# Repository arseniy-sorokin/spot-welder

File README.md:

# spot-welder
Spot welder controller for Warsaw Hackerspace (hackerspace.pl)

Based on work of Albert van Dalen http://www.avdweb.nl/arduino/hardware-interfacing/spot-welder-controller.html

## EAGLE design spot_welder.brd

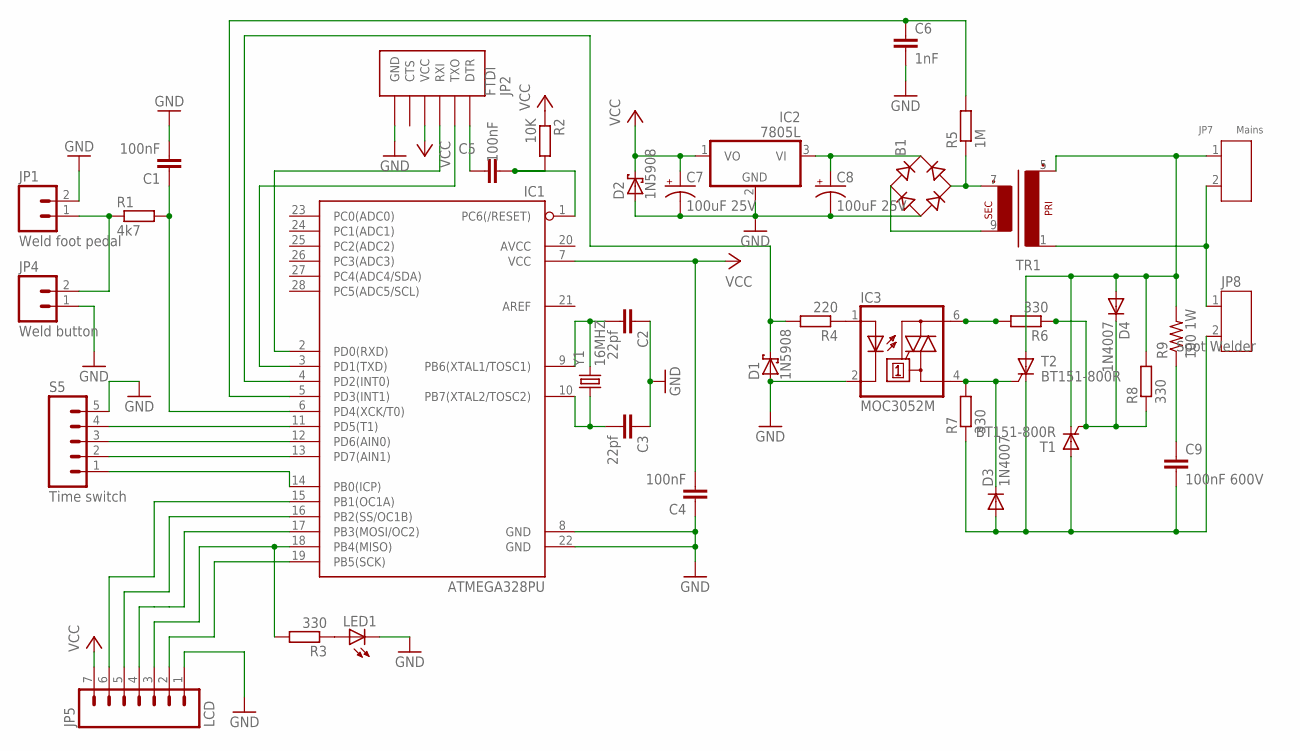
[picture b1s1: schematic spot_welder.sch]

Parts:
B1: B-DIL
C1: 100nF; CAP-PTH-5MM
C2, C3: 22pf; C025-024X044
C4, C5: 100nF; C025-024X044
C6: 1nF; C025-024X044
C7, C8: 100uF 25V; CPOL-RADIAL-100UF-25V
C9: 100nF 600V; C15B5
D1, D2: 1N5908; C4111-15
D3, D4: 1N4007; DO41-10
IC1: ATMEGA328PU; DIL28-3
IC2: 7805L; TO92
IC3: MOC3052M; DIL06
JP1: Weld foot pedal; 1X02_LOCK
JP2: FTDI; FTDI_DEVICE_SIDE
JP4: Weld button; 1X02_LOCK
JP5: LCD; 1X07_NO_SILK
JP7: Mains; H2-5.0-10.5X8.0MM
JP8: Spot Welder; H2-5.0-10.5X8.0MM
LED1: LEDLD260; LD260
R1: 4k7; 0204/7
R2: 10K; 0204/7
R3, R6, R7, R8: 330; 0204/7
R4: 220; 0204/7
R5: 1M; 0204/7
R9: 100 1W; AXIAL-0.6
S5: Time switch; 1X05_NO_SILK
T1, T2: BT151-800R; TO220CS
TR1: EI30-1
Y1: 16MHZ; HC49/S

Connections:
GND: B1.-, C1.2, C2.1, C3.1, C4.1, C6.2, C7.2 (-), C8.2 (-), D1.A, D2.A, IC1.8 (GND), IC1.22 (GND), IC2.2 (GND), IC3.2 (C), JP1.2, JP2.P$6 (GND), JP4.1, JP5.1, LED1.K (C), S5.5
unnamed: B1.AC2, R5.1, TR1.7 (S3)
unnamed: B1.+, C8.1 (+), IC2.3 (VI)
unnamed: C9.2, D3.A, JP8.2, R7.1, T1.A, T2.C
unnamed: B1.AC1, TR1.9 (S4)
unnamed: JP7.2, JP8.1, TR1.1
unnamed: D3.C, IC3.4 (A1), R7.2, T2.G
unnamed: C5.1, JP2.P$1 (DTR)
unnamed: IC3.6 (A2), R6.2
unnamed: IC3.1 (A), R4.1
unnamed: D4.A, JP7.1, R8.2, R9.P$2 (2), T1.C, T2.A, TR1.5 (P2)
unnamed: C9.1, R9.P$1 (1)
unnamed: D4.C, R6.1, R8.1, T1.G
unnamed: C6.1, IC1.5 (PD3(INT1)), R5.2
unnamed: C5.2, IC1.1 (PC6(/RESET)), R2.2
unnamed: D1.C, IC1.4 (PD2(INT0)), R4.2
unnamed: C2.2, IC1.9 (PB6(XTAL1/TOSC1)), Y1.2
unnamed: C3.2, IC1.10 (PB7(XTAL2/TOSC2)), Y1.1
unnamed: IC1.11 (PD5(T1)), S5.4
unnamed: IC1.3 (PD1(TXD)), JP2.P$2 (TXO)
unnamed: IC1.2 (PD0(RXD)), JP2.P$3 (RXI)
unnamed: JP1.1, JP4.2, R1.1
unnamed: C1.1, IC1.6 (PD4(XCK/T0)), R1.2
unnamed: IC1.12 (PD6(AIN0)), S5.3
unnamed: IC1.13 (PD7(AIN1)), S5.2
unnamed: IC1.14 (PB0(ICP)), S5.1
unnamed: LED1.A, R3.1
unnamed: IC1.18 (PB4(MISO)), JP5.3, R3.2
unnamed: IC1.15 (PB1(OC1A)), JP5.6
unnamed: IC1.16 (PB2(SS/OC1B)), JP5.5
unnamed: IC1.17 (PB3(MOSI/OC2)), JP5.4
unnamed: IC1.19 (PB5(SCK)), JP5.2
VCC: C4.2, C7.1 (+), D2.C, IC1.7 (VCC), IC2.1 (VO), JP2.P$4 (VCC), JP5.7, R2.1

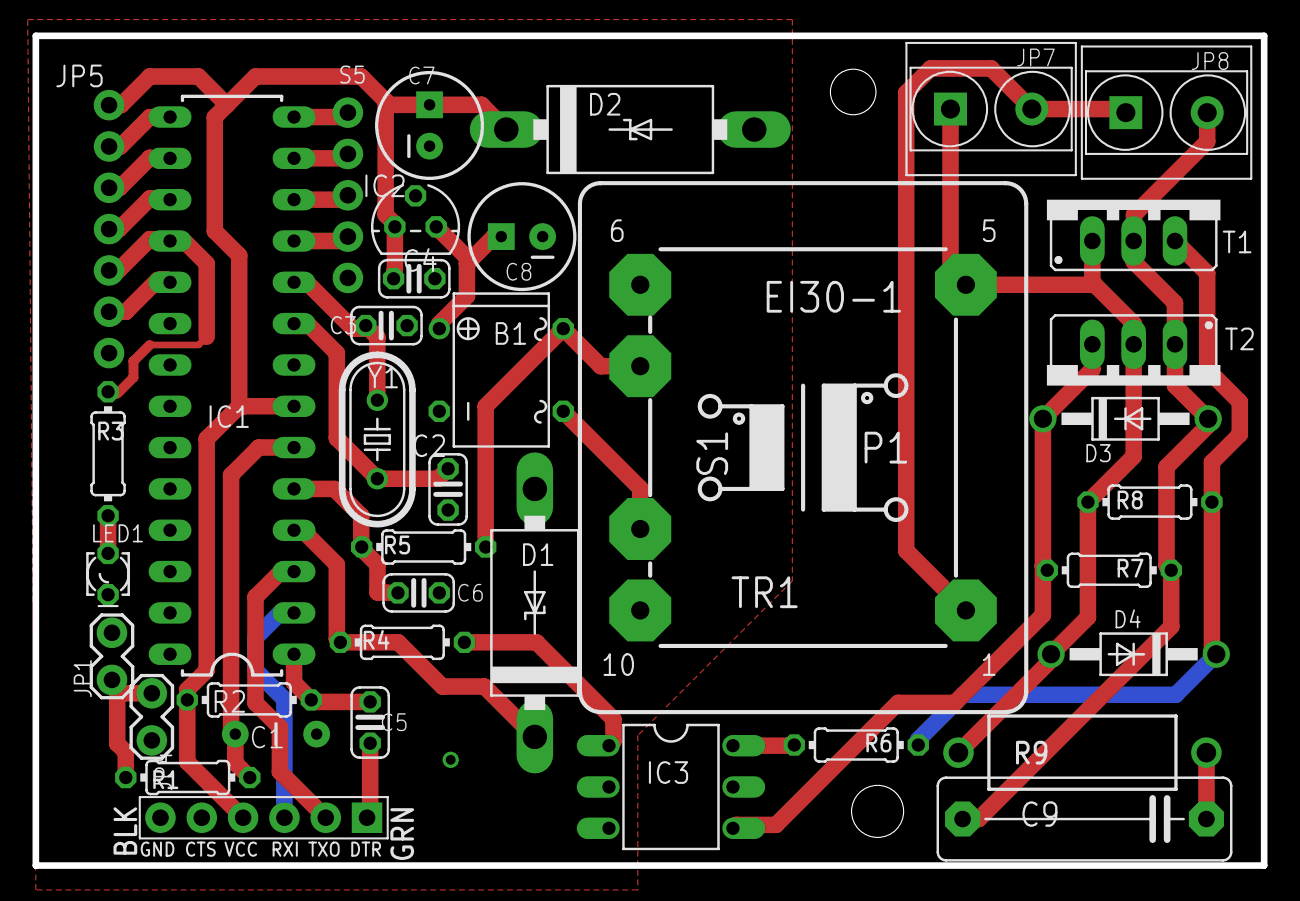
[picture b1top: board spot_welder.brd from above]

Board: 2 copper layers, 75.5 x 51.0 mm, 38 parts (0 on the bottom side), 33 nets.

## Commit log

2016-12-02 Added Eagle schematics and layout
2016-12-03 added VCC & GND planes
2016-12-03 rerouted
2016-12-03 prepared for printing
2016-12-03 added pdf with dimensions
2016-12-03 replaced pdf
2016-12-06 limited ground plane to low-voltage part; fixed angles on traces

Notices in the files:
parts and their libraries:
SparkFun-Capacitors: Licensing: Creative Commons ShareAlike 4.0 International - https://creativecommons.org/licenses/by-sa/4.0
